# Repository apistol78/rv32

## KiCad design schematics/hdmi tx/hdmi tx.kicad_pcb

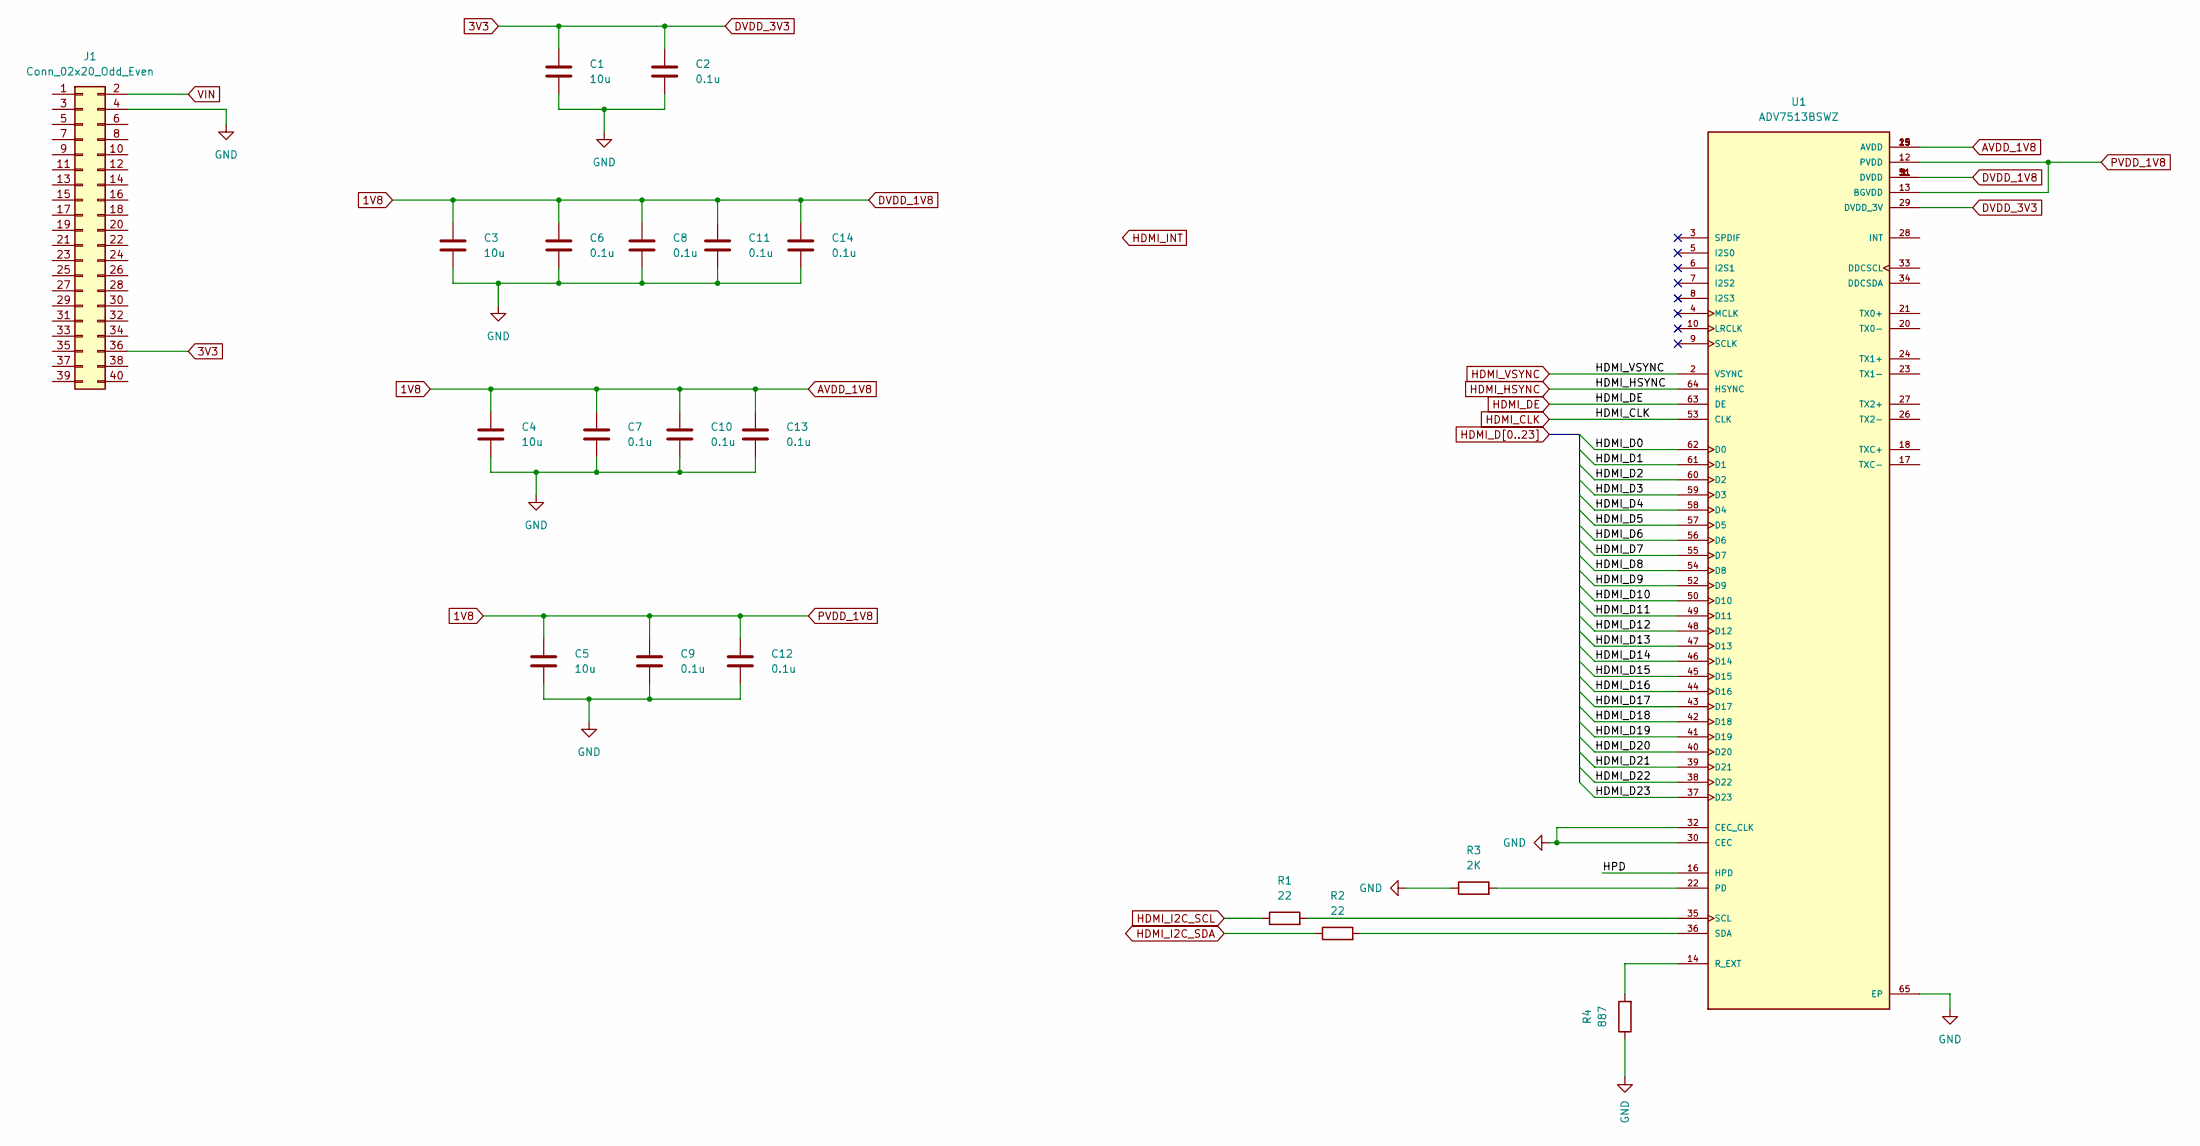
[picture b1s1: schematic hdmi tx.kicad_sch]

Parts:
C1, C3, C4, C5: 10u; C_0603_1608Metric
C2, C6, C7, C8, C9, C10, C11, C12, C13, C14: 0.1u; C_0603_1608Metric
J1: Conn_02x20_Odd_Even; PinSocket_2x40_P1.27mm_Vertical
R1, R2: 22; R_1206_3216Metric
R3: 2K; R_1206_3216Metric
R4: 887; R_1206_3216Metric
U1: ADV7513BSWZ; QFP50P1200X1200X160-65N; PARTREV B

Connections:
3V3: C1.1, C2.1, J1.36, U1.29 (DVDD_3V)
/HPD: U1.16 (HPD)
GND: C1.2, C2.2, C3.2, C4.2, C5.2, C6.2, C7.2, C8.2, C9.2, C10.2, C11.2, C12.2, C13.2, C14.2, J1.4, R3.1, R4.1, U1.30 (CEC), U1.32 (CEC_CLK), U1.65 (EP)
HDMI_CLK: U1.53 (CLK)
HDMI_D0: U1.62 (D0)
HDMI_D1: U1.61 (D1)
HDMI_D2: U1.60 (D2)
HDMI_D3: U1.59 (D3)
HDMI_D4: U1.58 (D4)
HDMI_D5: U1.57 (D5)
HDMI_D6: U1.56 (D6)
HDMI_D7: U1.55 (D7)
HDMI_D8: U1.54 (D8)
HDMI_D9: U1.52 (D9)
HDMI_D10: U1.50 (D10)
HDMI_D11: U1.49 (D11)
HDMI_D12: U1.48 (D12)
HDMI_D13: U1.47 (D13)
HDMI_D14: U1.46 (D14)
HDMI_D15: U1.45 (D15)
HDMI_D16: U1.44 (D16)
HDMI_D17: U1.43 (D17)
HDMI_D18: U1.42 (D18)
HDMI_D19: U1.41 (D19)
HDMI_D20: U1.40 (D20)
HDMI_D21: U1.39 (D21)
HDMI_D22: U1.38 (D22)
HDMI_D23: U1.37 (D23)
HDMI_DE: U1.63 (DE)
HDMI_HSYNC: U1.64 (HSYNC)
HDMI_I2C_SCL: R1.1
HDMI_I2C_SDA: R2.1
HDMI_VSYNC: U1.2 (VSYNC)
unnamed: R1.2, U1.35 (SCL)
unnamed: R2.2, U1.36 (SDA)
unnamed: R3.2, U1.22 (PD)
unnamed: R4.2, U1.14 (R_EXT)
VIN: J1.2

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
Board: 2 copper layers, 20 parts (0 on the bottom side), 8 nets, no tracks yet.
